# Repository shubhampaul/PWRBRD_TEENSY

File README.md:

# PWRBRD_TEENSY
Power Board - Teensy interface Eagle CAD design for Robocon'15

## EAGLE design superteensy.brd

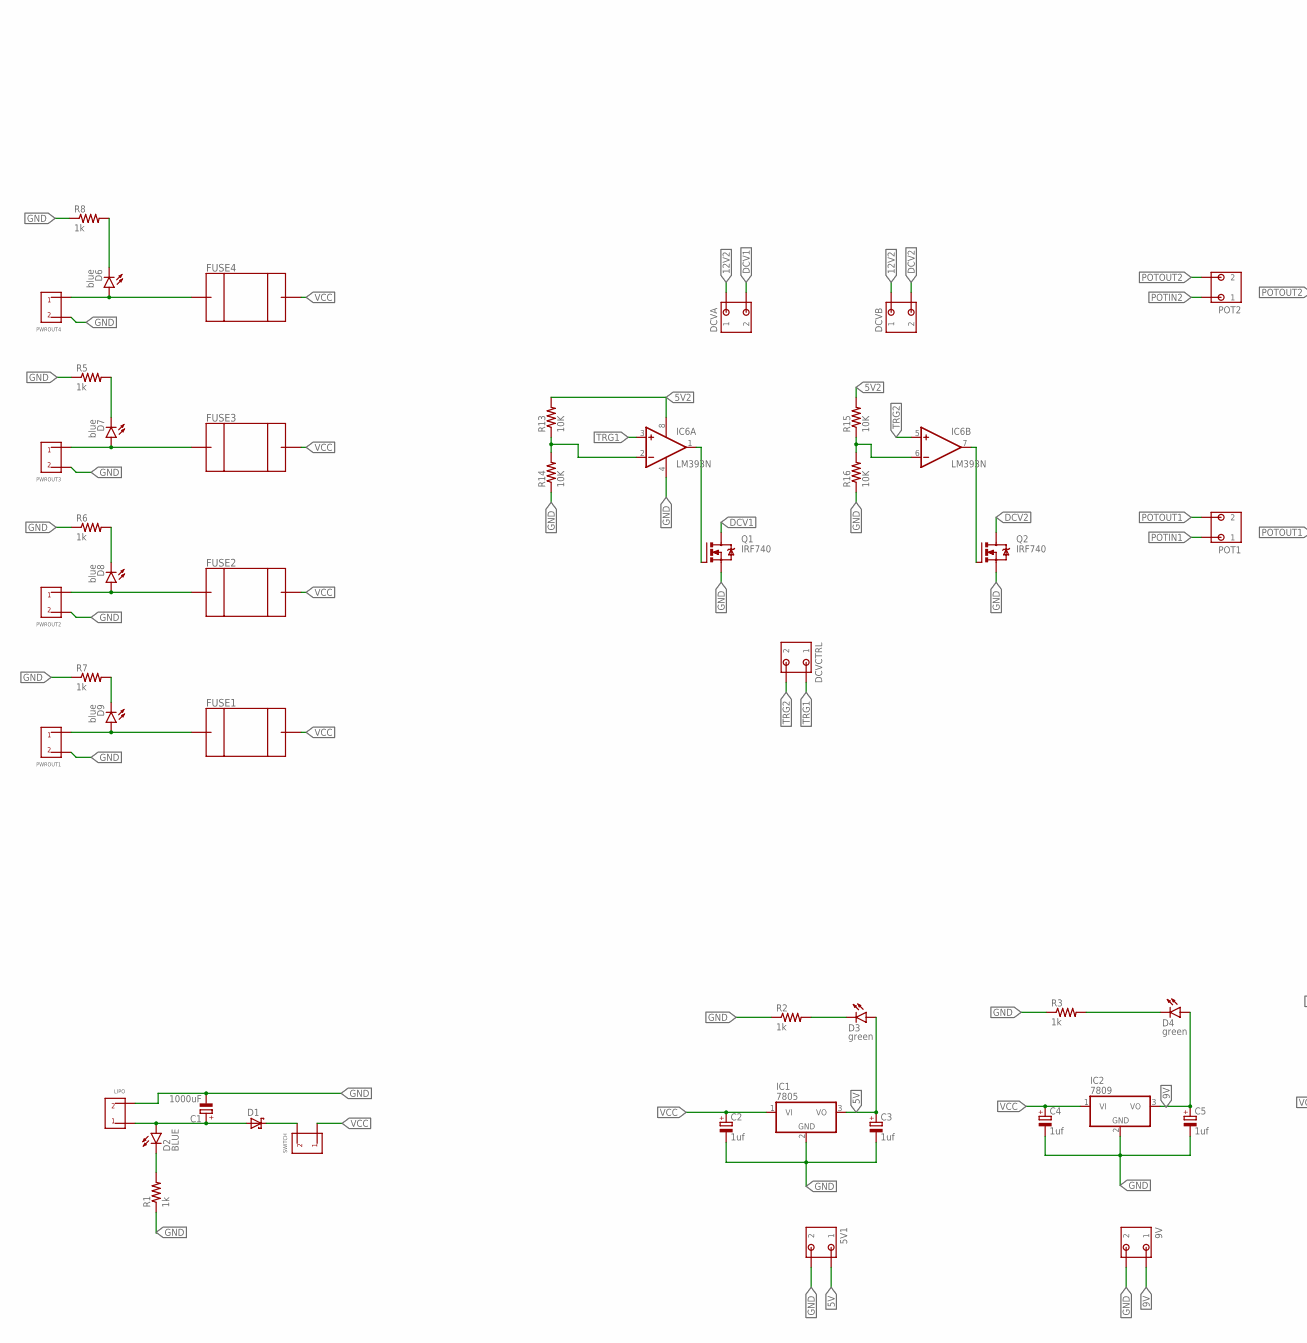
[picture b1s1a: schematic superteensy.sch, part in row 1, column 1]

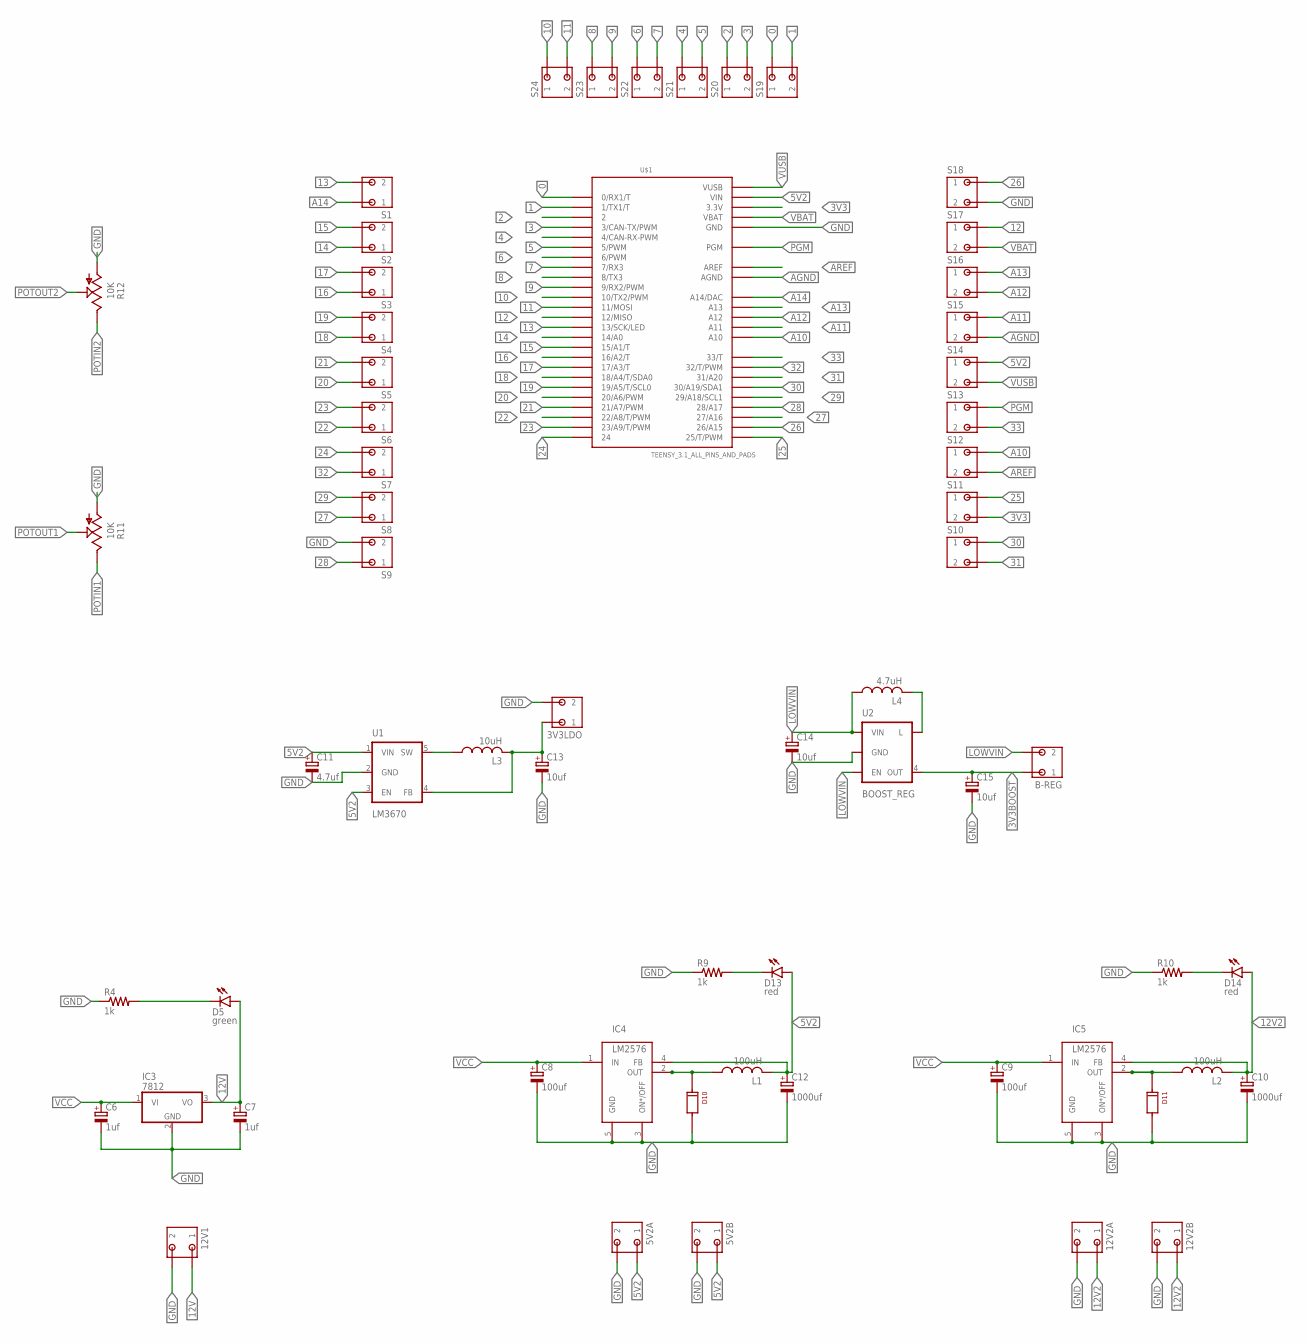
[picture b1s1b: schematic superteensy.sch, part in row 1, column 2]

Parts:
3V3LDO, 5V1, 5V2A, 5V2B, 9V, 12V1, 12V2A, 12V2B: SPTBA2-B2; SPTB
B-REG: SPTBA2-B2; SPTB
C1: 1000uF; E7,5-16
C2, C3, C4, C5, C6, C7: 1uf; E2-5
C8, C9: 100uf; E2,5-6E
C10, C12: 1000uf; E7,5-16
C11: 4.7uf; E2-5
C13, C14, C15: 10uf; E2-5
D1: SCHOTTKY-DIODEP6T15; P6T15
D2: BLUE; LED5MM
D3, D4, D5: green; LED5MM
D6, D7, D8, D9: blue; LED5MM
D10, D11: 1N5822
D13, D14: red; LED5MM
DCVA: SPTBA2-B2; SPTB
DCVB: SPTBA2-B2; SPTB
DCVCTRL: SPTBA2-B2; SPTB
FUSE1, FUSE2, FUSE3, FUSE4: CPT-FUSE; CPT-FUSES
IC1: 7805; 78XX
IC2: 7809; 78XX
IC3: 7812; 78XX
IC4, IC5: LM2576
IC6: LM393N; DIL08
L1, L2: 100uH; 0204/7
L3: 10uH; 0204/7
L4: 4.7uH; 0204/7
LIPO: SCREW_XT-60
POT1, POT2: SPTBA2-B2; SPTB
PWROUT1, PWROUT2, PWROUT3, PWROUT4: SCREW_XT-60
Q1, Q2: IRF740; TO220BV
R1, R2, R3, R4, R5, R6, R7, R8, R9, R10: 1k; 0204/7
R11, R12: 10K; CA6V
R13, R14, R15, R16: 10K; 0204/7
S1, S2, S3, S4, S5, S6, S7, S8, S9, S10, S11, S12, S13, S14, S15, S16, S17, S18, S19, S20, S21, S22, S23, S24: SPTBA2-B2; SPTB
SWITCH: SCREW_XT-60
U1: LM3670; SOT23-5
U2: BOOST_REG; SOT23-5
U$1: TEENSY_3.1_ALL_PINS_AND_PADS; TEENSY_3.1_ALLPINS

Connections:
0: S19.A1 (1), S19.A2 (1), U$1.0 (0/RX1/T)
1: S19.B1 (2), S19.B2 (2), U$1.1 (1/TX1/T)
2: S20.A1 (1), S20.A2 (1), U$1.2
3: S20.B1 (2), S20.B2 (2), U$1.3 (3/CAN-TX/PWM)
3V3: S11.B1 (2), S11.B2 (2), U$1.3.3V, U$1.3.3V1 (3.3V), U$1.3.3V2 (3.3V)
3V3BOOST: B-REG.A1 (1), B-REG.A2 (1), C15.+, U2.4 (OUT)
4: S21.A1 (1), S21.A2 (1), U$1.4 (4/CAN-RX-PWM)
5: S21.B1 (2), S21.B2 (2), U$1.5 (5/PWM)
5V: 5V1.A1 (1), 5V1.A2 (1), C3.+, D3.A, IC1.3 (VO)
5V2: 5V2A.A1 (1), 5V2A.A2 (1), 5V2B.A1 (1), 5V2B.A2 (1), C11.+, C12.+, D13.A, IC4.4 (FB), IC6.8 (V+), L1.2, R13.2, R15.2, S14.A1 (1), S14.A2 (1), U1.1 (VIN), U1.3 (EN), U$1.VIN
6: S22.A1 (1), S22.A2 (1), U$1.6 (6/PWM)
7: S22.B1 (2), S22.B2 (2), U$1.7 (7/RX3)
8: S23.A1 (1), S23.A2 (1), U$1.8 (8/TX3)
9: S23.B1 (2), S23.B2 (2), U$1.9 (9/RX2/PWM)
9V: 9V.A1 (1), 9V.A2 (1), C5.+, D4.A, IC2.3 (VO)
10: S24.A1 (1), S24.A2 (1), U$1.10 (10/TX2/PWM)
11: S24.B1 (2), S24.B2 (2), U$1.11 (11/MOSI)
12: S17.A1 (1), S17.A2 (1), U$1.12 (12/MISO)
12V: 12V1.A1 (1), 12V1.A2 (1), C7.+, D5.A, IC3.3 (VO)
12V2: 12V2A.A1 (1), 12V2A.A2 (1), 12V2B.A1 (1), 12V2B.A2 (1), C10.+, D14.A, DCVA.A1 (1), DCVA.A2 (1), DCVB.A1 (1), DCVB.A2 (1), IC5.4 (FB), L2.2
13: S1.B1 (2), S1.B2 (2), U$1.13 (13/SCK/LED)
14: S2.A1 (1), S2.A2 (1), U$1.14/A0
15: S2.B1 (2), S2.B2 (2), U$1.15/A1 (15/A1/T)
16: S3.A1 (1), S3.A2 (1), U$1.16/A2 (16/A2/T)
17: S3.B1 (2), S3.B2 (2), U$1.17/A3 (17/A3/T)
18: S4.A1 (1), S4.A2 (1), U$1.18/A4 (18/A4/T/SDA0)
19: S4.B1 (2), S4.B2 (2), U$1.19/A5 (19/A5/T/SCL0)
20: S5.A1 (1), S5.A2 (1), U$1.20/A6 (20/A6/PWM)
21: S5.B1 (2), S5.B2 (2), U$1.21/A7 (21/A7/PWM)
22: S6.A1 (1), S6.A2 (1), U$1.22/A8 (22/A8/T/PWM)
23: S6.B1 (2), S6.B2 (2), U$1.23/A9 (23/A9/T/PWM)
24: S7.B1 (2), S7.B2 (2), U$1.24
25: S11.A1 (1), S11.A2 (1), U$1.25 (25/T/PWM)
26: S18.A1 (1), S18.A2 (1), U$1.26 (26/A15)
27: S8.A1 (1), S8.A2 (1), U$1.27 (27/A16)
28: S9.A1 (1), S9.A2 (1), U$1.28 (28/A17)
29: S8.B1 (2), S8.B2 (2), U$1.29 (29/A18/SCL1)
30: S10.A1 (1), S10.A2 (1), U$1.30 (30/A19/SDA1)
31: S10.B1 (2), S10.B2 (2), U$1.31 (31/A20)
32: S7.A1 (1), S7.A2 (1), U$1.32 (32/T/PWM)
33: S13.B1 (2), S13.B2 (2), U$1.33 (33/T)
A10: S12.A1 (1), S12.A2 (1), U$1.A10
A11: S15.A1 (1), S15.A2 (1), U$1.A11
A12: S16.B1 (2), S16.B2 (2), U$1.A12
A13: S16.A1 (1), S16.A2 (1), U$1.A13
A14: S1.A1 (1), S1.A2 (1), U$1.A14 (A14/DAC)
AGND: S15.B1 (2), S15.B2 (2), U$1.AGND
AREF: S12.B1 (2), S12.B2 (2), U$1.AREF
DCV1: DCVA.B1 (2), DCVA.B2 (2), Q1.D
DCV2: DCVB.B1 (2), DCVB.B2 (2), Q2.D
GND: 3V3LDO.B1 (2), 3V3LDO.B2 (2), 5V1.B1 (2), 5V1.B2 (2), 5V2A.B1 (2), 5V2A.B2 (2), 5V2B.B1 (2), 5V2B.B2 (2), 9V.B1 (2), 9V.B2 (2), 12V1.B1 (2), 12V1.B2 (2), 12V2A.B1 (2), 12V2A.B2 (2), 12V2B.B1 (2), 12V2B.B2 (2), C1.-, C2.-, C3.-, C4.-, C5.-, C6.-, C7.-, C8.-, C9.-, C10.-, C11.-, C12.-, C13.-, C14.-, C15.-, D10.-, D11.-, IC1.2 (GND), IC2.2 (GND), IC3.2 (GND), IC4.3 (ON*/OFF), IC4.5 (GND), IC5.3 (ON*/OFF), IC5.5 (GND), IC6.4 (V-), LIPO.P$2, PWROUT1.P$2, PWROUT2.P$2, PWROUT3.P$2, PWROUT4.P$2, Q1.S, Q2.S, R1.1, R2.1, R3.1, R4.1, R5.1, R6.1, R7.1, R8.1, R9.1, R10.1, R11.A, R12.A, R14.1, R16.1, S9.B1 (2), S9.B2 (2), S18.B1 (2), S18.B2 (2), U1.2 (GND), U2.2 (GND), U$1.GND, U$1.GND1 (GND), U$1.GND2 (GND)
LOWVIN: B-REG.B1 (2), B-REG.B2 (2), C14.+, L4.1, U2.1 (VIN), U2.3 (EN)
unnamed: C1.+, D1.A, D2.A, LIPO.P$1
unnamed: D1.C, SWITCH.P$2
unnamed: D3.K (C), R2.2
unnamed: D2.K (C), R1.2
unnamed: D4.K (C), R3.2
unnamed: D5.K (C), R4.2
unnamed: D6.A, FUSE4.P$1, PWROUT4.P$1
unnamed: D7.A, FUSE3.P$1, PWROUT3.P$1
unnamed: D8.A, FUSE2.P$1, PWROUT2.P$1
unnamed: D9.A, FUSE1.P$1, PWROUT1.P$1
unnamed: D9.K (C), R7.2
unnamed: D8.K (C), R6.2
unnamed: D7.K (C), R5.2
unnamed: D6.K (C), R8.2
unnamed: D13.K (C), R9.2
unnamed: D10.+, IC4.2 (OUT), L1.1
unnamed: D11.+, IC5.2 (OUT), L2.1
unnamed: D14.K (C), R10.2
unnamed: IC6.1 (OUT), Q1.G
unnamed: IC6.7 (OUT), Q2.G
unnamed: IC6.2 (-IN), R13.1, R14.2
unnamed: IC6.6 (-IN), R15.1, R16.2
unnamed: L3.1, U1.5 (SW)
unnamed: 3V3LDO.A1 (1), 3V3LDO.A2 (1), C13.+, L3.2, U1.4 (FB)
unnamed: L4.2, U2.5 (L)
PGM: S13.A1 (1), S13.A2 (1), U$1.PGM
POTIN1: POT1.A1 (1), POT1.A2 (1), R11.E
POTIN2: POT2.A1 (1), POT2.A2 (1), R12.E
POTOUT1: POT1.B1 (2), POT1.B2 (2), R11.S
POTOUT2: POT2.B1 (2), POT2.B2 (2), R12.S
TRG1: DCVCTRL.A1 (1), DCVCTRL.A2 (1), IC6.3 (+IN)
TRG2: DCVCTRL.B1 (2), DCVCTRL.B2 (2), IC6.5 (+IN)
VBAT: S17.B1 (2), S17.B2 (2), U$1.VBAT
VCC: C2.+, C4.+, C6.+, C8.+, C9.+, FUSE1.P$2, FUSE2.P$2, FUSE3.P$2, FUSE4.P$2, IC1.1 (VI), IC2.1 (VI), IC3.1 (VI), IC4.1 (IN), IC5.1 (IN), SWITCH.P$1
VUSB: S14.B1 (2), S14.B2 (2), U$1.VUSB

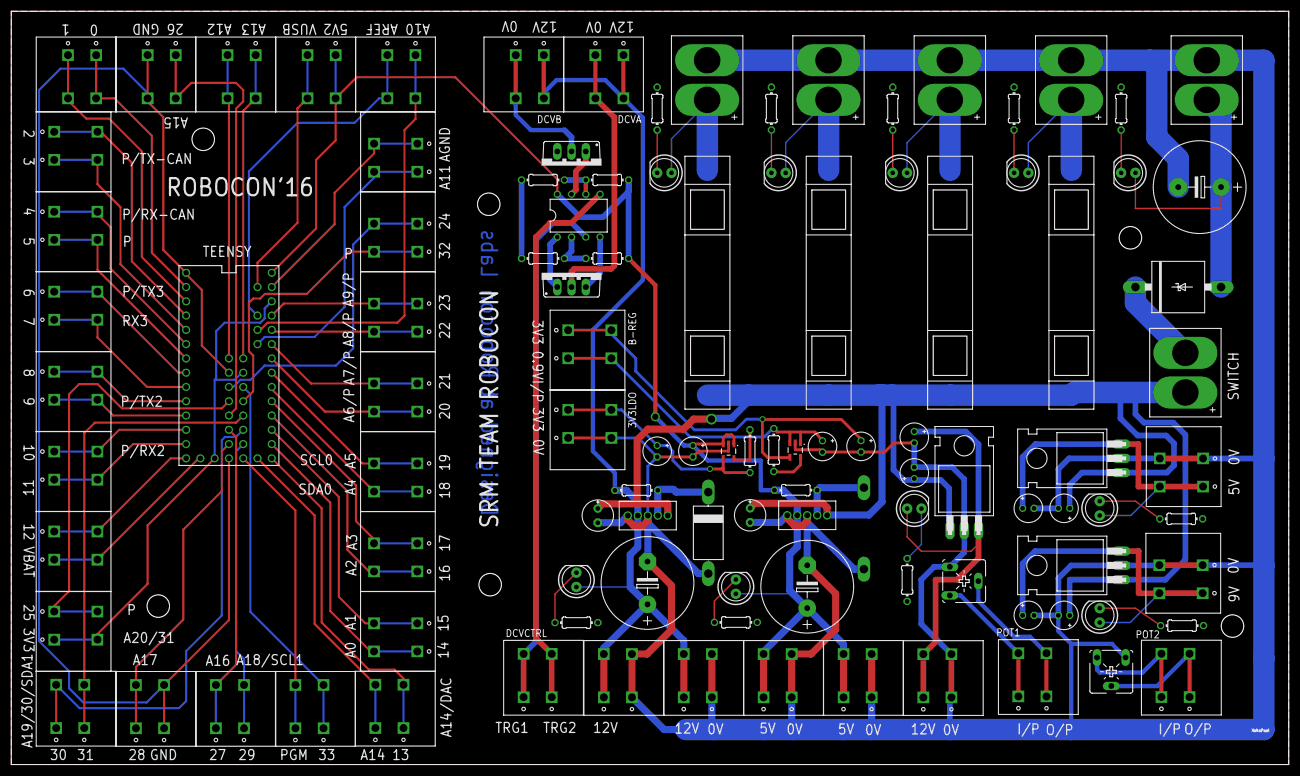
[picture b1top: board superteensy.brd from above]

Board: 2 copper layers, 227.3 x 134.0 mm, 107 parts (1 on the bottom side), 87 nets.

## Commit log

2016-10-29 Added board files and schematic

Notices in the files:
parts and their libraries:
SparkFun-LED: Licensing: Creative Commons ShareAlike 4.0 International - https://creativecommons.org/licenses/by-sa/4.0
